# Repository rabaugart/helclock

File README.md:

# helclock

## Text

10 Zeilen, 11 Spalten

    ESKISTAFÜNF
    ZEHNZWANZIG
    DREIVIERTEL
    VORFUNKNACH
    HALBAELFÜNF
    EINSXAMZWEI
    DREIPMJVIER
    SECHSNLACHT
    SIEBENZWÖLF
    ZEHNEUNKUHR

Anpassungen

    ESBISTAFÜNF
      -
    ZEHNZWANZIG
    DREIVIERTEL
    VORBESONACH
       ----
    HALBAELFÜNF
    EINSDOMZWEI
        --
    DREIHELVIER
        ---
    SECHSRAACHT
         --
    SIEBENZWÖLF
    ZEHNEUNFUHR
           -

## Segmente

## LED-Varianten

- Pollin-[Sortiment](https://www.pollin.de/p/sort-led-neopixel-programmierbar-800567) programmierbar, mit SK6812 und WS2812B, 40 Stck 2,95€.
- Digikey-[Kategorie](https://www.digikey.de/de/products/filter/leds-adressierbar-spezialanwendungen/126) für programmierbare LEDs.
- Adafruit-Neopixel 5050 bei [berrybase](https://www.berrybase.de/adafruit-neopixel-5050-rgb-led-mit-integriertem-treiber-10-stueck)
  oder [Mouser](https://www.mouser.de/ProductDetail/Adafruit/3094?qs=SV%252B0z0o3NTt%2F2YK7E3w5Rg%3D%3D) 100 Stck, 25,76€.
- THT-Leds mit WS2812 bei [Berrybase](https://www.berrybase.de/adressierbare-ws2812-rgb-led-pth-5mm-diffus-5er-pack),
  von [Sparkfun](https://learn.sparkfun.com/tutorials/ws2812-breakout-hookup-guide#addressable-through-hole-led)
- Neopixel [Nano](https://www.adafruit.com/product/4684) castellated, 10 Stück, 4,24€ bei [Antratek](https://www.antratek.de/neopixel-nano-2020-rgb-leds-10-pack-ws2812b)
- Berrybase [Streifen](https://www.berrybase.de/digitaler-led-rgb-neopixel-stripe-ip65-vergossen-30-leds-schwarz-50cm-mit-kabelanschluss)
  mit 30 LEDs auf 50cm.
- LED-[Matrix](https://eckstein-shop.de/WaveShare-RGB-Full-Color-LED-Matrix-Panel-64x64-Pixels-3mm-Pitch-Adjustable-Brightness) bei Eckstein
- Adressierbare [LED-Streifen](https://www.pololu.com/product/3086) bei Pololu
- Adressierbare [LED-Streifen](https://www.tme.eu/de/details/n013060ca3sa1/lichtquellen-led-bander/ipixel-led/) bei TME.
- Einzelne, adressierbare, programmierbare [LED](https://eu.robotshop.com/products/5mm-adressable-rgb-led-5pk) THT bei RobotShop
- Einzelne, programmierbare LEDs auf Breakout bei [Watterott](https://shop.watterott.com/WS2812B-Breakout-Intelligent-RGB-LED-5-Stk) mit WS2812B-Controller.
THT-LEDs

### Adressierbare LEDs, THT

Infos bei [Sparkfun](https://learn.sparkfun.com/tutorials/ws2812-breakout-hookup-guide#addressable-through-hole-led)

NeoPixel-[Library](https://github.com/adafruit/Adafruit_NeoPixel) von Adafruit

### Berrybase-Streifen

Neopixel 5050

### Neopixel Nano 2020, castelleted

Verwendet WS2812B, könnte evtl Worldsemi [2812-2020](http://world-semi.com/ws2812-family/) entsprechen.

Listing bei [Mouser](https://www.mouser.de/ProductDetail/Adafruit/4684?qs=DPoM0jnrROWIv9%2FMCIm5vw%3D%3D&_gl=1*jup3r4*_ga*dW5kZWZpbmVk*_ga_15W4STQT4T*dW5kZWZpbmVk*_ga_1KQLCYKRX3*dW5kZWZpbmVk).

## Analoge LED-Treiber

Kategorie bei [Mouser](https://www.mouser.de/c/semiconductors/driver-ics/led-lighting-driver-ics/)

Als Schieberegister beispielsweise von [TI](https://www.mouser.de/ProductDetail/Texas-Instruments/TLC5916INE4?qs=vPP9GyyTAo06VIPRtWrixw%3D%3D)

## Controller

- [ESP32-C6](https://docs.espressif.com/projects/esp-dev-kits/en/latest/esp32c6/esp32-c6-devkitm-1/user_guide.html)

## Distributoren

- [Antratek](https://www.antratek.de/)

## Alternative Projekte

- RPi-[Wordclock](https://github.com/bk1285/rpi_wordclock)

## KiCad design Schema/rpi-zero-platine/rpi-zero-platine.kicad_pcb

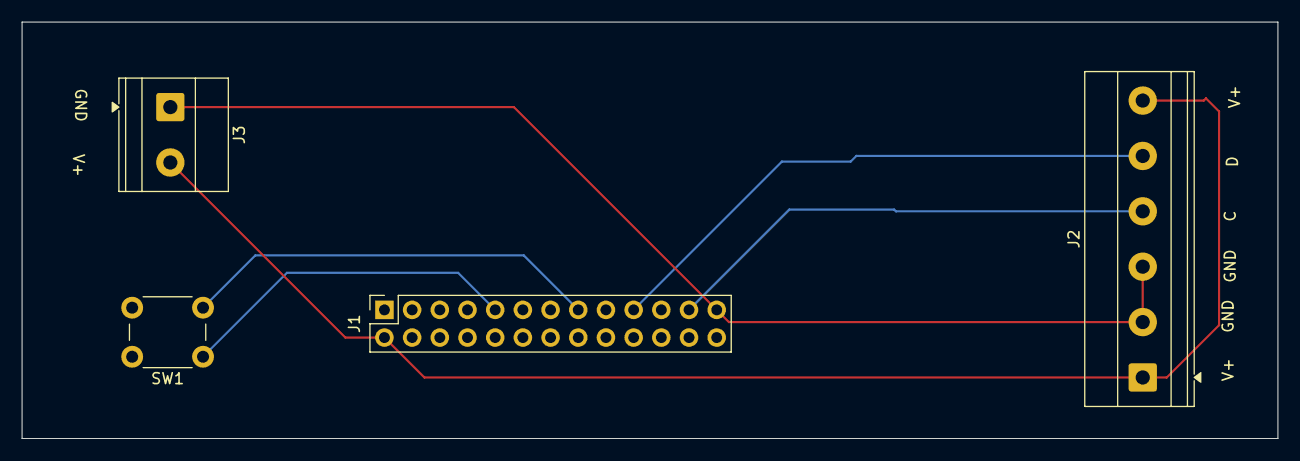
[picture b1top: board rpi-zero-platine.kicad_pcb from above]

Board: 2 copper layers, 115.2 x 38.2 mm, 4 parts (0 on the bottom side), 6 nets.

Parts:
J1: GPIO; PinSocket_2x13_P2.54mm_Vertical
J2: LED Out A; TerminalBlock_Phoenix_MKDS-1,5-6-5.08_1x06_P5.08mm_Horizont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
J3: LED Out B; TerminalBlock_Phoenix_MKDS-1,5-2-5.08_1x02_P5.08mm_Horizont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
SW1: SW_DIP_x02; SW_PUSH_6mm_H4.3mm

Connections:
+5V: J1.2 (VCC), J2.1, J2.6, J3.2 (LEDB+)
/Clock: J1.23 (SPI0.SCLK), J2.4
/Data: J1.19 (SPI0.MOSI), J2.5
GND: J1.25 (GND), J2.2, J2.3, J3.1 (LEDB-)
unnamed: J1.9, SW1.1
unnamed: J1.15, SW1.2

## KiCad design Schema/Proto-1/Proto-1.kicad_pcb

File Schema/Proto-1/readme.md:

# Schema Development Board

Ressourcen:

- [Kicad](https://github.com/espressif/kicad-libraries) Library von Espressif

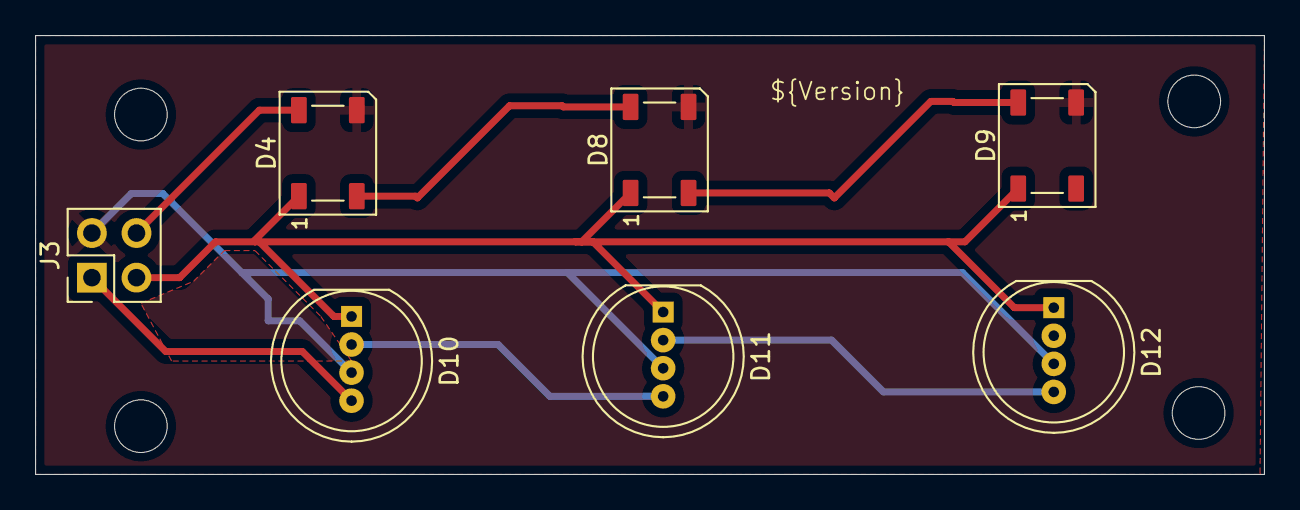
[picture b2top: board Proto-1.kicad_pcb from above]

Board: 2 copper layers, 70.0 x 25.0 mm, 7 parts (0 on the bottom side), 8 nets.

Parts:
D4, D8, D9: LED-Brightek; LED-SMD-Brightek-N0M50S18IC_5.0x5.0mm_P3.2mm
D10, D11, D12: LED_THT-OSTWMN8132A; LED_D8.0mm-4
J3: Conn_02x02_Counter_Clockwise; PinHeader_2x02_P2.54mm_Vertical

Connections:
+5V: D4.1 (VDD), D8.1 (VDD), D9.1 (VDD), D10.1 (VCC), D11.1 (VCC), D12.1 (VCC), J3.3
GND: D4.3 (VSS), D8.3 (VSS), D9.3 (VSS), D10.3 (VSS), D11.3 (VSS), D12.3 (VSS), J3.2
unnamed: D4.4 (DIN), J3.4
unnamed: D4.2 (DOUT), D8.4 (DIN)
unnamed: D8.2 (DOUT), D9.4 (DIN)
unnamed: D10.4 (DIN), J3.1
unnamed: D10.2 (DOUT), D11.4 (DIN)
unnamed: D11.2 (DOUT), D12.4 (DIN)

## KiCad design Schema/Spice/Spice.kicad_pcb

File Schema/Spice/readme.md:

# Schema Prototyp 1, Version P1-0.3

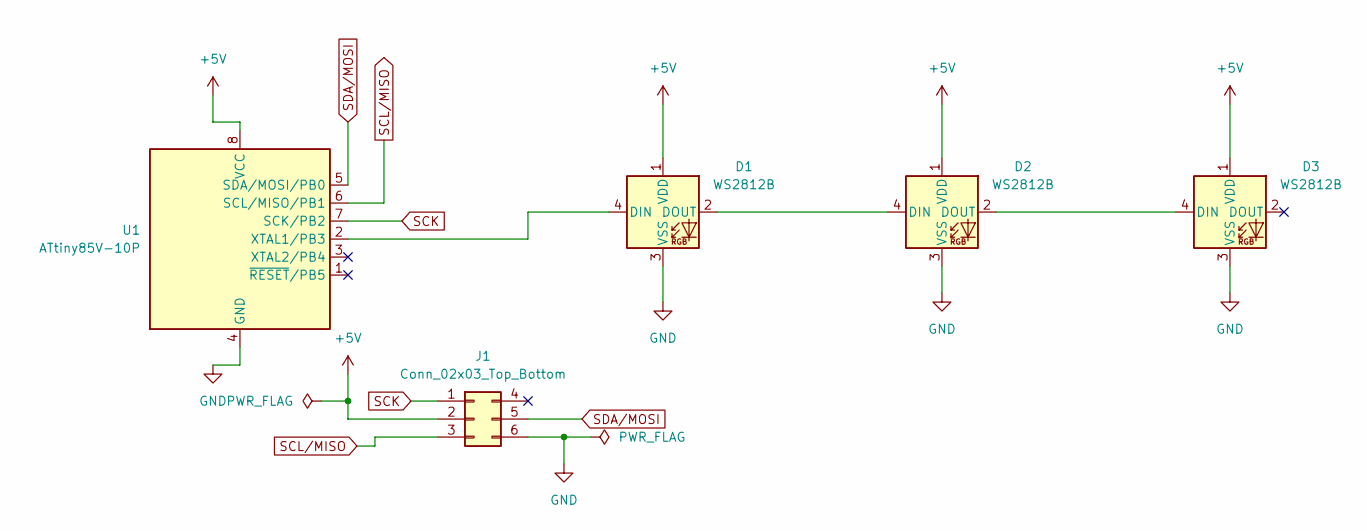
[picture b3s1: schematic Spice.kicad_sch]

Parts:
D1, D2, D3: WS2812B; LED_WS2812B_PLCC4_5.0x5.0mm_P3.2mm
J1: Conn_02x03_Top_Bottom; IDC-Header_2x03_P2.54mm_Horizontal
U1: ATtiny85V-10P; SO-8_3.9x4.9mm_P1.27mm

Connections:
+5V: D1.1 (VDD), D2.1 (VDD), D3.1 (VDD), J1.2, U1.8 (VCC)
GND: D1.3 (VSS), D2.3 (VSS), D3.3 (VSS), J1.6, U1.4 (GND)
unnamed: D1.4 (DIN), U1.2 (XTAL1/PB3)
unnamed: D1.2 (DOUT), D2.4 (DIN)
unnamed: D2.2 (DOUT), D3.4 (DIN)
SCK: J1.1, U1.7 (SCK/PB2)
SCL/MISO: J1.3, U1.6 (SCL/MISO/PB1)
SDA/MOSI: J1.5, U1.5 (SDA/MOSI/PB0)

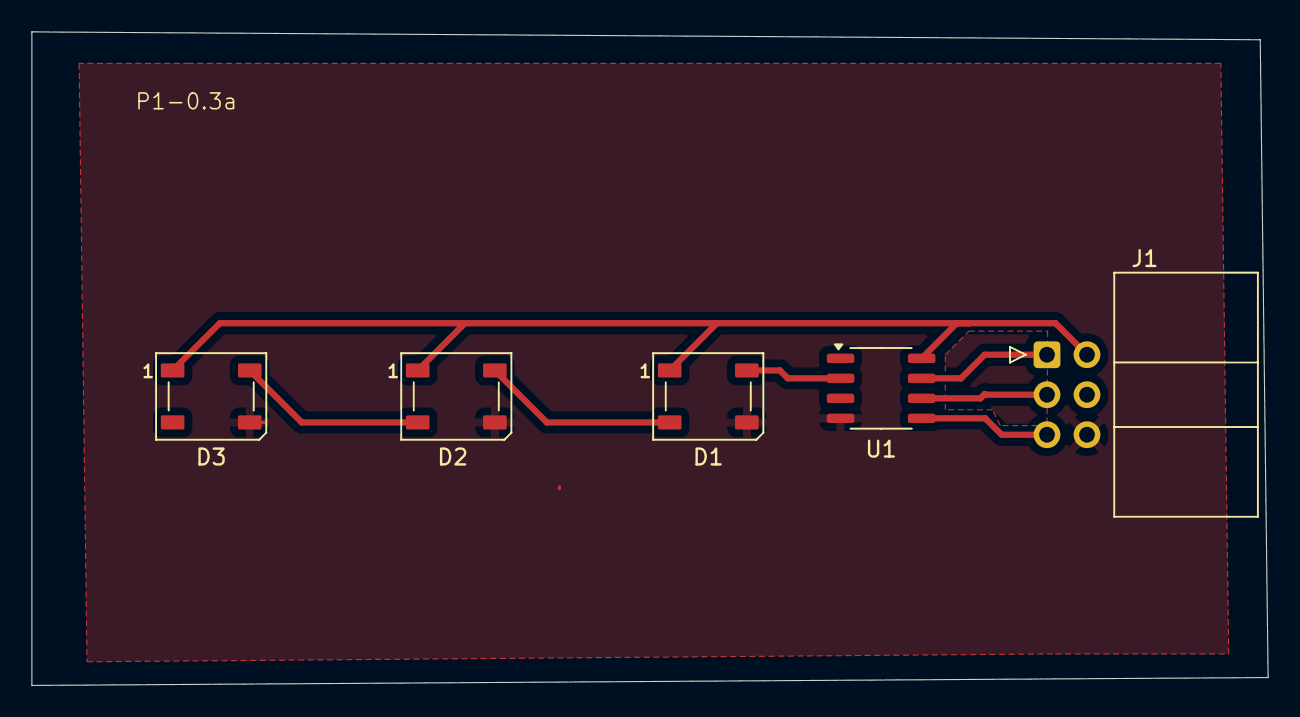
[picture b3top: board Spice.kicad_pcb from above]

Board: 2 copper layers, 78.5 x 41.5 mm, 5 parts (0 on the bottom side), 8 nets.

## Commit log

2025-09-04 Beschreibe LED-Varianten
2025-09-06 Weitere Notizen
2025-09-06 Frontplatte
2025-09-09 Weitere Infos, Datenblätter
2025-09-10 1. Bestellung
2025-09-11 Beginne Prototyp 1
2025-09-11 Teste Exportmöglichkeiten
2025-09-11 Ändere Konnektor, korrigiere Pfadbreiten
2025-09-11 Erzeuge Output für p1-0.2
2025-09-11 Räume Schema auf
2025-09-11 Ergänze eine Zone ohne Net am Konnektor
2025-09-12 Verkleinere die Fläche, füge Bohrungen ein
2025-09-12 Bereite Version 0.4a vor
2025-09-12 Benenne um Spice -> Proto-1
2025-09-12 Benenne Files um
2025-09-12 Erstelle Schema für B
2025-09-13 Beginne Devboard
2025-09-13 Erstelle PCB für Devboard, ersetzte Proto-1-Board
2025-09-13 Bereite DB1-0.4 vor
2025-09-13 Typo
2025-09-13 Fixe Dateinamen
2025-09-13 Bereite Proto-1-0.5a vor, setze Sheet-Propery "exclude from board"
2025-10-06 Datenblatt ws2801
2025-10-29 Erste Skizze mit Querwand
2025-10-29 Mache Anzahl parametrisch
2025-10-30 Füge Wände ein
2025-10-30 Füge Nuten mit Spiel in die Wände ein
2025-10-30 Verkleinere Wanddicke und Wandspiel
2025-10-30 Füge Grundplatte hinzu
2025-10-30 Füge Front hinzu
2025-11-01 Benenne um, füge Font hinzu
2025-11-01 Füge Step-Datei für Pi Zero 2 W hinzu
2025-11-01 Füge Mockup für Pi Zero hinzu
2025-11-01 Füge Zungen in Grundplatte hinzu
2025-11-02 Füge Gruppen in den Baum ein
2025-11-02 Exportiere STL
2025-11-02 Füge vertikales Spiel in den Wandgehrungen hinzu
2025-11-02 Vollständige Frontplatte mit Font
2025-11-04 Füge Fräsecken und Überstande in Quer- und Längswand ein
2025-11-04 Erzeuge Link für Grundplatte
2025-11-04 Füge Fräsecken in Grundplatte ein
2025-11-04 Vergrößere Segmentlänge von 30 auf 31mm, vergrößere Wandhöhe von 25 auf 30mm
2025-11-05 Füge Zeichnung hinzu
2025-11-05 Verschiebe den Raspi, fixe die fehlende Multitransform in der Grundplatte
2025-11-10 Füge Bemaßung für Raster hinzu
2025-11-15 Füge Nasen hinzu
2025-11-15 Vergrößere die Schlitze in der Grundplatte
2025-11-15 Korrigiere Nasenlaenge, aktualisiere Zeichnung
2025-11-16 Verschiebe die Bemassung der Längswand
2025-11-16 Füge Fräsradien an der Nase hinzu
2025-11-16 Lösche kaputtes Mass in der Zeichnung an der Längswand
2025-11-16 Ändere Sichtbarkeit auf Montage
2025-11-16 Füge Fräsradien an den Zapfen der Querwand hinzu
2025-11-16 Exportiere STL und STEP, verschiebe Zeichnung, entferne alte Exports
2025-11-18 Create ElectronicComponents
    Added possible electronic components at tme.eu
2025-11-29 Füge Meanwell Netzteil hinzu
2025-11-29 Frontplatte mit Space-Future
2025-11-29 Füge Pi Mockup hinzu
2025-11-29 Montiere Meanwell-Netzteil
2025-11-30 Aktuelle Zeichnung
2025-11-30 Vergrößere Massstab für LED in TechDraw
2025-11-30 Korrigiere Massstabsangaben in TechDraw
2025-11-30 Vergrößere Reihenabstand, verschiebe Raspi, exportiere neu
2025-11-30 Füge Fräsecken an den Nasen der Querwand ein
2025-11-30 Füge Fräsecken an den Zungen der Längswand ein
2025-11-30 Grundplattendicke -> 5mm, Wandhöhe -> 35mm, Frontplattenüberstand -> 50mm, Grundplattenüberstand -> 45mm
2025-11-30 Füge Überstände als benannte Constraints in Basisabmessungen ein
2025-11-30 Füge Seitenteile hinzu
2025-11-30 Aktualisiere Zeichnung
2025-11-30 Füge weitere Daten in die Zeichnung ein
2025-12-01 Exportiere aktuellen Stand
2025-12-01 Vergrößere auf 10x11, Überhänge += 5mm, verlinke Netzteil
2025-12-01 Verbessere die Zeichnung, insbesondere die Bemaßung
2025-12-01 Setze Datum in der Zeichnung auf auto
2025-12-02 Füge Schriftart hinzu
2025-12-02 Verbessere Bemaßung an Längs- und Querwand
2025-12-02 Verringere die Banddicke auf 2,2 mm
2025-12-02 Setze die Banddicke zurück und Schlitzhöhe auf Banddicke + 0,2 mm (statt 1mm)
2025-12-02 Füge Querwand aussen hinzu
2025-12-02 Exporte Teile als Mesh
2025-12-04 Setze Tagfeld in Zeichnung auf m-0.5
2025-12-04 Füge Details ein
2025-12-07 Füge LPD8806-Python-Library hinzu
2025-12-07 Füge Datenblätter für Pi 3 B hinzu, dokumentiere
2025-12-07 Passe das Example an
2025-12-07 Korrigiere Code
2025-12-07 Deaktiviere Wheel
2025-12-07 Verbessere Initialisierung
2025-12-07 Gamma-Frage
2025-12-08 Too buggy
2025-12-08 tled1
2025-12-08 Es zuckt
2025-12-08 1 LED leuchtet korrekt
2025-12-08 Mehrere LEDs
2025-12-08 sendn
2025-12-08 Mehr Farben
2025-12-09 c3 Uhr
2025-12-09 Kleinigkeit
2025-12-09 Beginn hclock
2025-12-09 Löschen fehlerhaftes LPD8806 Beispiel
2025-12-10 Füge Datenblatt pi zero w hinzu
2025-12-10 Dokumentiere, beginne Koordinatensystem
2025-12-10 Wortindexe
2025-12-11 Muster
2025-12-12 Datenblatt Pegelwandler
2025-12-12 Erlaube Multiplikation Color*float
2025-12-12 Operator ==
2025-12-12 Neues Muster
2025-12-12 Generatoren
2025-12-12 Blink-Generator
2025-12-13 index_koordinaten und Textausgabe
2025-12-13 Teste curses
2025-12-13 Testmuster für Strang
2025-12-13 Erste curses clock
2025-12-13 Fixe default_zeit
2025-12-13 Reduziere Update-Zyklen
2025-12-13 zeit_spi_generator
2025-12-13 Rendere UHR nur zur vollen Stunden
2025-12-13 Ersetze fünfundzwanzig durch fünf vor halb
2025-12-13 Füge hclock-Generator in Muster ein
2025-12-13 Fix q-Bug in clcurses
2025-12-13 Starte Index unten rechts statt unten links
2025-12-13 Korrigiere Dokumentation
2025-12-14 Notizen zu ANSI-Farben
2025-12-14 Reset shell
2025-12-14 Testmuster
2025-12-14 Aktiviere auf Target
2025-12-14 Schalte Uhr häufiger
2025-12-15 Adaptiere Text der Frontplatte Füge extra Worte ein Verschiebe Tests in das c3 Modul
2025-12-15 Lagere Wort-Enums aus
2025-12-15 Dokumentation
2025-12-16 ColWortGenerator
2025-12-16 Skizziere Platine für rpi zero
2025-12-16 Teste ColWortGenerator in muster.py
2025-12-16 Korrigiere Zeitstempel
2025-12-16 Fixe Zeitstempel
2025-12-16 Ändere Footprint der Schraubklemmen auf Phoenix mit 3D-Model
2025-12-16 Ändere Footprint des Switches
2025-12-17 Überarbeite Platine
2025-12-17 Beschriftung
2025-12-17 Korrigiere Testmuster
2025-12-18 Starte Flask
2025-12-18 Flask 1
2025-12-18 Flask 2
2025-12-18 Flask 3
2025-12-18 Flask 4
2025-12-18 Flask 5, dyn Generators
2025-12-18 Flask 6
2025-12-19 Flask Color Slider
2025-12-19 Flask websockets
2025-12-19 Websocket auf 0.0.0.0
2025-12-20 Server stop
2025-12-20 Verschiebe flask
2025-12-20 Extrahiere template und script
2025-12-20 Erste, bidirektionale Kommunikation
2025-12-20 Mache ws_server_port konfigurierbar
2025-12-20 set_color_slider_value
2025-12-20 Füge style und buttons hinzu
2025-12-23 Links
2025-12-24 Erzeuge Modul server, beginne quart Broker
2025-12-24 Baue 2 Buttons, die Nachrichten senden
2025-12-26 Baue UI auf
2025-12-27 Initiales Setzen des Generators
2025-12-28 Übertrage Status an Client
2025-12-28 Erzeuge UI anhand der Status-Nachricht
2025-12-29 Überarbeite Controler, baue Tests
2025-12-29 Integriere überarbeiteten Controler in Webapp
2025-12-29 Baue Kommando COL_UPDATE ein
2025-12-29 Baue Generatoren weiter, räume auf, verwende 0.0.0.0
2025-12-29 Generiere Farben
2025-12-29 Optimiere Zeiten
2025-12-29 Rotiere Testmuster
2025-12-29 Entferne flask, fixe Test
2025-12-29 Verwende grid-Layout
2025-12-29 Reduziere Logging
2025-12-30 Reaktiviere stopper
2025-12-30 Extrahiere agenerator
2025-12-30 Reorganisiere den Controler
2025-12-30 Reorganisiere weiter
2025-12-30 Reorganisiere
2025-12-31 Spiele mit TestGen, rekonfiguriere ProdGen, benenne ConStatus um in GenSetBase
2025-12-31 Füge Farbkasten zum UI hinzu
2025-12-31 Justiere System Service
2025-12-31 Erzeuge TestGen1 aus bisherigem ClockGen
2025-12-31 Übersetze COL_SECTs in passendere Namen
2025-12-31 Ergänze COL_SECTs
2026-01-01 Setze Generatoren fort
2026-01-01 Fixe ClockGen
2026-01-01 Verwende farbmap in ClockGen
2026-01-01 Korrigiere Fehler bei Verwendung der Farbmap in ColWortGenerator
2026-01-01 Vervollständige TestGen2 in ProdGenSet
2026-01-01 Korrigiere TestGen2
2026-01-01 Korrigiere noch ein Mal
2026-01-01 Prüfe WebSocket und starte ggf. neu
2026-01-01 Baue Blocker ein
2026-01-01 Mache Kontext konfigurierbar
2026-01-02 Verwende mehr Farben in ColWortGenerator
2026-01-02 Verwende die Farben in ClockGen
2026-01-02 Verbessere Umschaltverhalten von ClockGen
2026-01-02 Verwemde aktuelle Zeit in feier_demo
2026-01-03 Kopiere Colors bei Initialisierung
2026-01-29 Füge Board-Bilder hinzu
2026-02-03 Lege Worte für Minuten an
2026-02-03 Erzeuge Zeitsätze mit Minuten
2026-02-03 Füge Minutenanzeige in Curses-Clock ein
2026-02-22 Korrigiere Fehler in hclock.index_range
2026-02-23 Mache Minutenanzeige konfigurierbar mit aktiviere_minutenanzeige
2026-02-23 Schalte Minuten-LEDs aus
2026-02-23 Serialisiere den Zustand
2026-02-25 3 POM-Teile, rechts mit Ausschnitt
2026-02-25 Aussparung PomOben für Kabel
